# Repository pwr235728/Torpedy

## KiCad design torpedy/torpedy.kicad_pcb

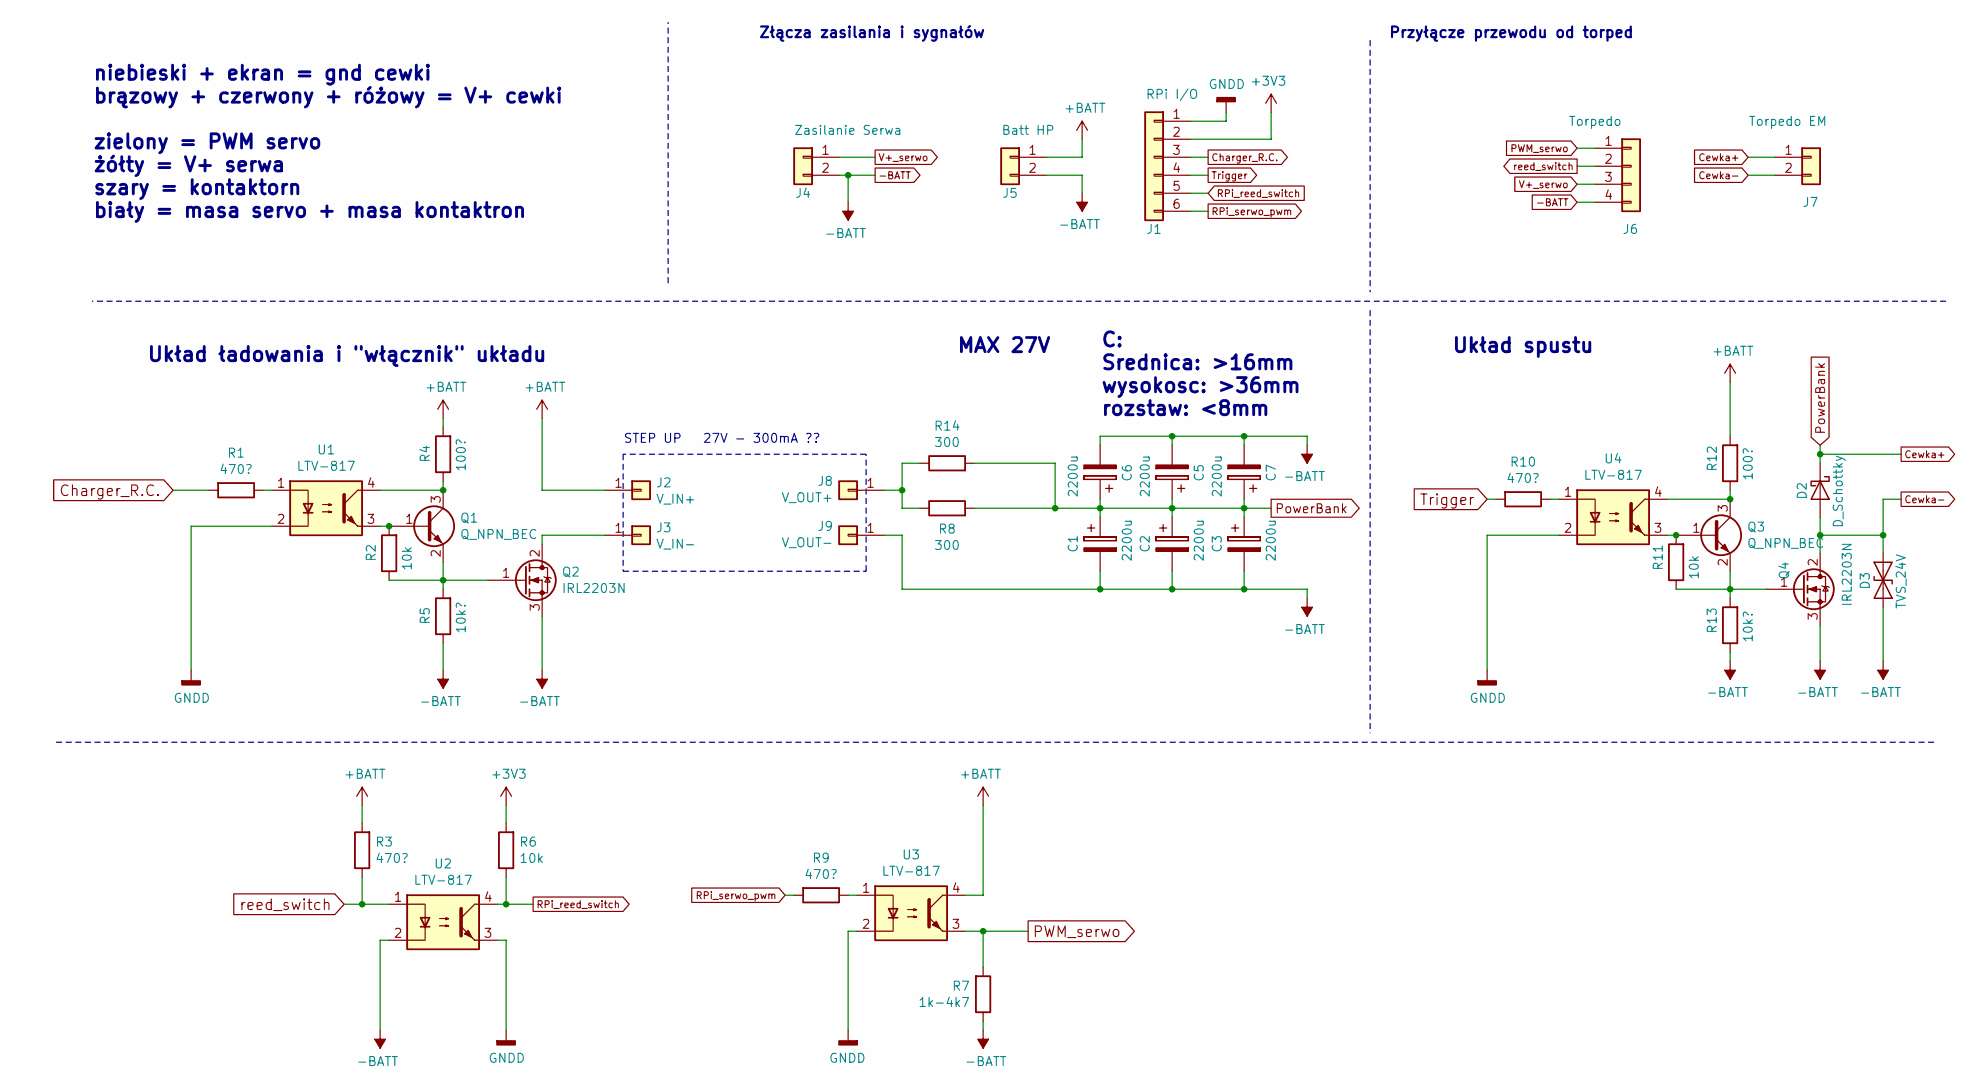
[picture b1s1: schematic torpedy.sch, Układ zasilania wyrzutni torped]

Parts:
C1, C2, C3, C5, C6, C7: 2200u; CP_Radial_D16.0mm_P7.50mm
D2: D_Schottky; D_SMC_Handsoldering
D3: TVS_24V; D_SMB_Handsoldering
J1: RPi I/O; Molex_SPOX_5267-06A_1x06_P2.50mm_Vertical
J2: V_IN+; PinHeader_1x01_P2.54mm_Vertical
J3: V_IN-; PinHeader_1x01_P2.54mm_Vertical
J4: Zasilanie Serwa; Molex_Mini-Fit_Jr_5566-02A_2x01_P4.20mm_Vertical
J5: Batt HP; Molex_Mini-Fit_Jr_5566-02A_2x01_P4.20mm_Vertical
J6: Torpedo; Molex_SPOX_5267-04A_1x04_P2.50mm_Vertical
J7: Torpedo EM; Molex_Mini-Fit_Jr_5566-02A_2x01_P4.20mm_Vertical
J8: V_OUT+; PinHeader_1x01_P2.54mm_Vertical
J9: V_OUT-; PinHeader_1x01_P2.54mm_Vertical
Q1, Q3: Q_NPN_BEC; SOT-23_Handsoldering
Q2, Q4: IRL2203N; TO-263-2
R1, R3, R9, R10: 470?; R_0805_2012Metric_Pad1.15x1.40mm_HandSolder
R2, R6, R11: 10k; R_0805_2012Metric_Pad1.15x1.40mm_HandSolder
R4, R12: 100?; R_0805_2012Metric_Pad1.15x1.40mm_HandSolder
R5, R13: 10k?; R_0805_2012Metric_Pad1.15x1.40mm_HandSolder
R7: 1k-4k7; R_0805_2012Metric_Pad1.15x1.40mm_HandSolder
R8, R14: 300; R_Axial_DIN0414_L11.9mm_D4.5mm_P20.32mm_Horizontal
U1, U2, U3, U4: LTV-817; SMDIP-4_W9.53mm

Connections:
+3V3: J1.2, R6.2
+BATT: J2.1, J5.1, R3.2, R4.2, R12.2, U3.4
-BATT: C1.2, C2.2, C3.2, C5.2, C6.2, C7.2, D3.2 (A2), J4.2, J5.2, J6.4, J9.1, Q2.3 (S), Q4.3 (S), R5.1, R7.1, R13.1, U2.2
Cewka+: C1.1, C2.1, C3.1, C5.1, C6.1, C7.1, D2.1 (K), J7.1, R8.2, R14.2
Cewka-: D2.2 (A), D3.1 (A1), J7.2, Q4.2 (D)
Charger_R.C.: J1.3, R1.2
GNDD: J1.1, U1.2, U2.3, U3.2, U4.2
unnamed: J3.1, Q2.2 (D)
unnamed: J8.1, R8.1, R14.1
unnamed: Q1.1 (B), R2.2, U1.3
unnamed: Q1.2 (E), Q2.1 (G), R2.1, R5.2
unnamed: Q1.3 (C), R4.1, U1.4
unnamed: Q3.1 (B), R11.2, U4.3
unnamed: Q3.2 (E), Q4.1 (G), R11.1, R13.2
unnamed: Q3.3 (C), R12.1, U4.4
unnamed: R1.1, U1.1
unnamed: R9.1, U3.1
unnamed: R10.1, U4.1
PWM_serwo: J6.1, R7.2, U3.3
RPi_reed_switch: J1.5, R6.1, U2.4
RPi_serwo_pwm: J1.6, R9.2
Trigger: J1.4, R10.2
V+_serwo: J4.1, J6.3
reed_switch: J6.2, R3.1, U2.1

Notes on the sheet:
27V - 300mA ??
STEP UP
Układ ładowania i "włącznik" układu
Układ spustu
niebieski + ekran = gnd cewki brązowy + czerwony + różowy = V+ cewki zielony = PWM servo żółty = V+ serwa szary = kontaktorn biały = masa servo + masa kontaktron
Złącza zasilania i sygnałów
Przyłącze przewodu od torped
MAX 27V
C: Srednica: >16mm wysokosc: >36mm rozstaw: <8mm

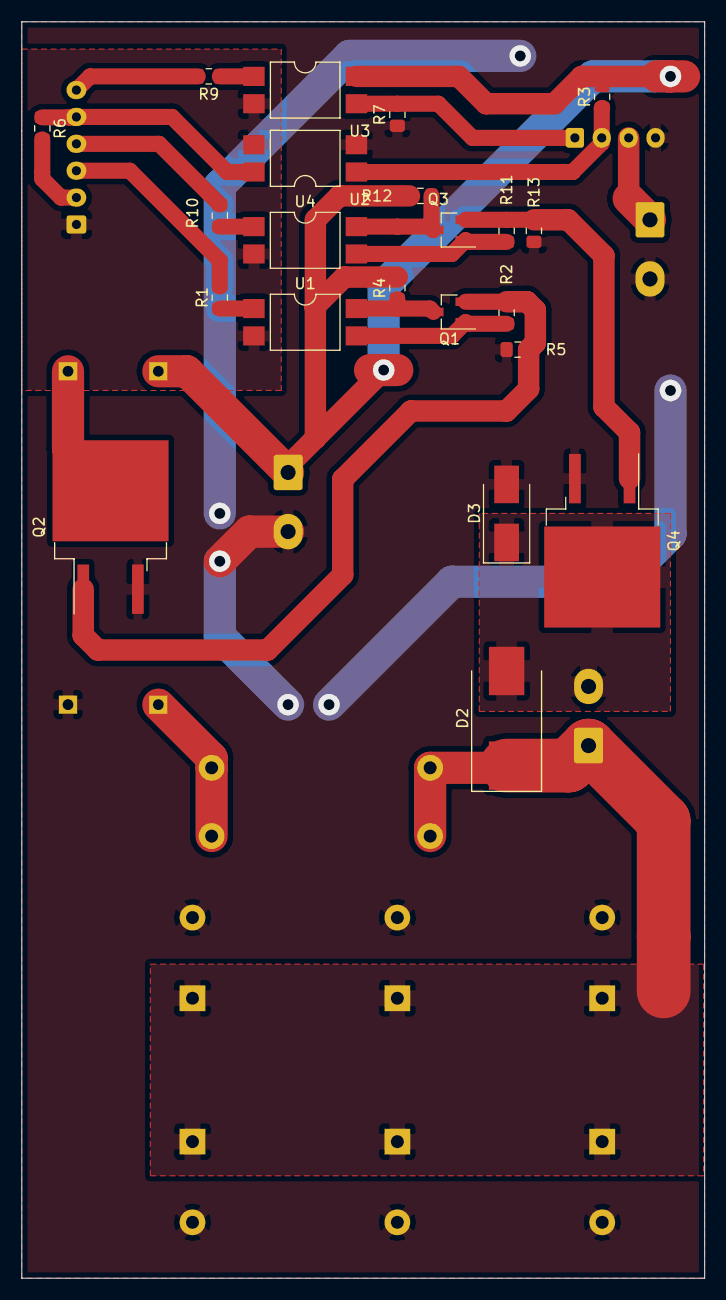
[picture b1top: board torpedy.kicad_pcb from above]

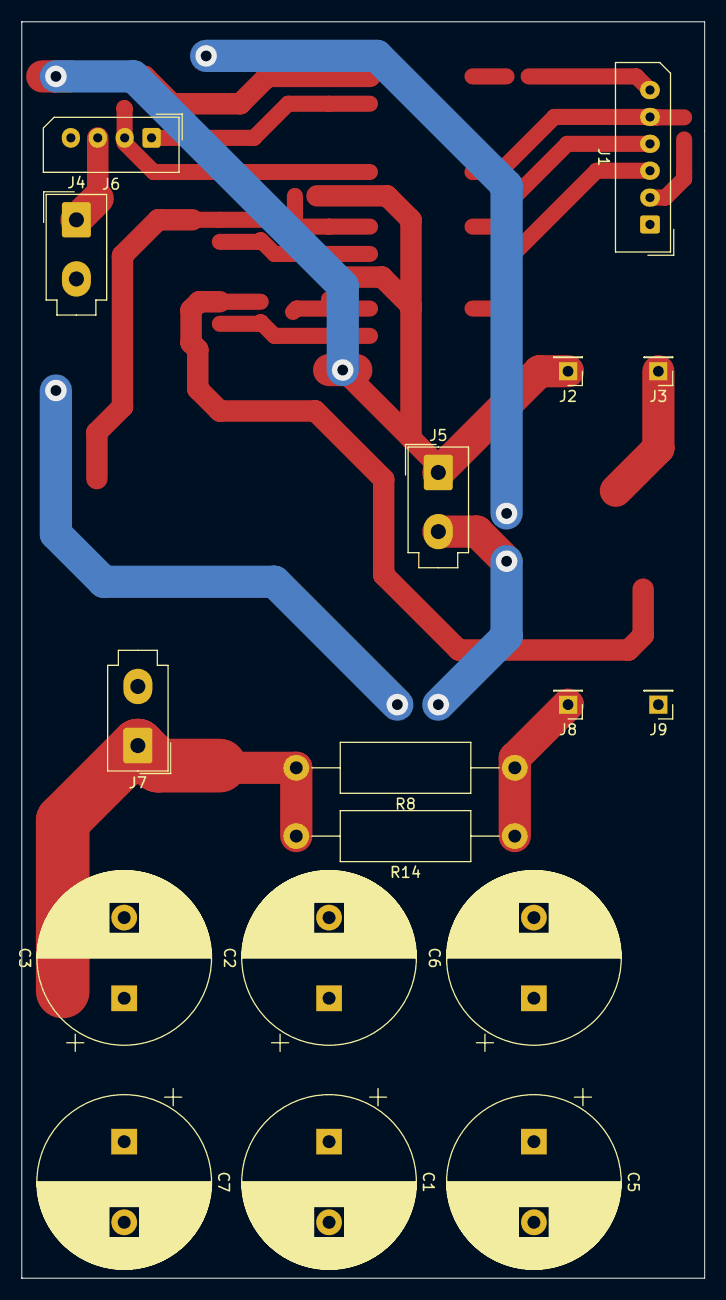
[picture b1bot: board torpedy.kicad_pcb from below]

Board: 2 copper layers, 63.5 x 116.8 mm, 39 parts (17 on the bottom side), 24 nets.

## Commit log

2019-07-16 kompletny
2019-07-16 kilka poprawek wartości elementow
2019-07-16 poprawki parametrów elementów
2019-07-16 Poprawki schematu
2019-07-17 Jprdl nic nie umie i gupi jeste
2019-07-17 Schemat pcb - początek
2019-07-17 wersja finalna
